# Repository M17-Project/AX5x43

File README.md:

# AX5x43
Test boards for the ON Semiconductor AX5043 and AX5243 RF transceiver chips.
#### The main purpose of this board is to test AX5x43's M17 support.

### Main differences between our board and other available out there
There are two major differences:
- the PWRAMP (AX5043) or TCXO_EN (AX5243) pin can be used as a sigma-delta modulator output for analog demodulation
- GPADC1 and GPADC2 pins can be used for analog frequency modulation (a VCO mode, if you will)

Note: There are no additional operational amplifiers nor filters in our design. Both modulator input and output are available at the pin header. ADC inputs can work in both differential and single-ended modes. Refer to the application note [AND9313/D](https://www.onsemi.com/pub/collateral/and9313-d.pdf).

### AX5043 PCB

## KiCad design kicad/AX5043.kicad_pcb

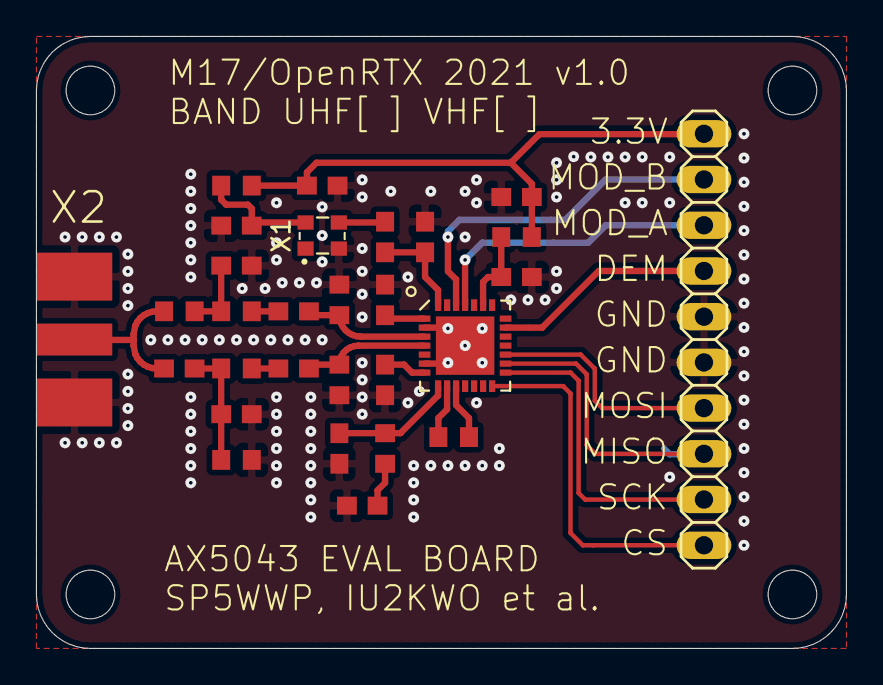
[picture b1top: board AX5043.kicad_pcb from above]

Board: 2 copper layers, 45.0 x 34.0 mm, 29 parts (0 on the bottom side), 26 nets.

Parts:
C1: 10p; C0603
C2: 6.8p; C0603
C3, C4: 100p; C0603
C5, C6: 4.3p; C0603
C7: 11p; C0603
C8: 5.6p; C0603
C9: 5.1p; C0603
C10, C12, C15: 10n; C0603
C11, C13: 100n; C0603
C14: 39p; C0603
JP1: PINHD-1X10; 1X10
R1, R2: 100nH; R0603
R3, R4: 43nH; R0603
R5, R6: 27nH; R0603
R7, R8: BEAD; R0603
R9: 10nH; R0603
R10: 12k; R0603
U1: AX5043; QFN28-5X5-WITH-CENTER-PAD
X1: 12.000MHz; ECS-TXO-2520
X2: SMA; J502-ND-142-0711-821_826

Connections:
+3V3: C11.1, C13.1, JP1.1, R7.2, R8.2
/CLK_REF: C1.2, C2.1, U1.28
/CS: JP1.10, U1.14
/DEMOD_OUT: JP1.4, U1.20
/MISO: JP1.8, U1.16
/MOD_IN_A: JP1.3, U1.25
/MOD_IN_B: JP1.2, U1.26
/MOSI: JP1.7, U1.17
/SCLK: JP1.9, U1.15
GND: C2.2, C3.2, C4.2, C7.1, C8.2, C10.1, C11.2, C12.1, C13.2, C14.2, C15.2, JP1.5, JP1.6, R1.1, R2.2, R6.2, U1.2, U1.6, U1.PAD, X1.2, X2.G@1, X2.G@2, X2.G@3, X2.G@4
unnamed: C1.1, X1.3
unnamed: C3.1, U1.1
unnamed: C4.1, U1.7
unnamed: C5.1, R2.1, U1.3
unnamed: C5.2, R3.1
unnamed: C6.1, R1.2, U1.4
unnamed: C6.2, R4.1
unnamed: C7.2, R3.2, R5.1
unnamed: C8.1, C9.2, R4.2, R6.1
unnamed: C9.1, R5.2, X2.1
unnamed: C10.2, R7.1, X1.4
unnamed: C12.2, R8.1, U1.23
unnamed: C14.1, R10.1, U1.8
unnamed: C15.1, R10.2
unnamed: R9.1, U1.9
unnamed: R9.2, U1.10

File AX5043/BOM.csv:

References,Qty,Description,Manufacturer,MPN
C1,1,10pF 0603,Yageo,CC0603JRNPO9BN100
C2,1,6.8pF 0603,Yageo,CC0603DRNPO9BN6R8
C3 C4,2,100pF 0603,Yageo,CC0603JRNPO9BN101
C5 C6,2,4.3pF 0603,Yageo,CC0603CRNPO9BN4R3
C7,1,11pF 0603,Yageo,CC0603JPNPO9BN110
C8,1,5.6pF 0603,Yageo,CC0603DRNPO9BN5R6
C9,1,5.1pF 0603,Yageo,CC0603CRNPO9BN5R1
C10 C12 C15,3,10nF 0603,Yageo,CC0603KRX7R9BB103
C11 C13,2,100nF 0603,Yageo,CC0603KRX7R9BB104
C14,1,39pF 0603,Yageo,CC0603JRNPO9BN390
JP1,1,CPL-CON-HEADER-THT-MALE,,
R1 R2,2,100nH 0603,Murata,LQW18ASR10G00D
R3 R4,2,43nH 0603,Murata,LQW18AN43NG00D
R5 R6,2,27nH 0603,Murata,LQW18AN27NG00D
R9,1,6.8nH 0603,Murata,LQW18AN6N8C00D
R10,1,12k 0603,Yageo,RC0603FR-0712KL
U1,1,AX5043,onsemi,AX5043-1-TW30
X1,1,12MHz TCXO 2520,ECS,ECS-TXO-2520MV-120-AY-TR
X2,1,SMA female connector PCB edge mount,RF Solutions,CON-SMA-EDGE-S

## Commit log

2021-08-16 Eagle and KiCad project files
2021-08-24 Rescued some missing symbols/footprint in KiCad project
2021-08-24 Add rounded corners
2021-09-09 Reorganised KiCad libraries
2021-09-09 New footprint for TCXO, model is ECS-TXO-2520
2021-09-13 Gerber files for PCB manufacturing
2021-09-13 Fixed some unconnected ground vias, re-generated gerber files
2021-09-13 Removed dangling trace, re-generated gerber files
2021-10-31 Added folder for AX5243 board, moved AX5043 files to a dedicated folder
2022-01-15 Changed value of VCO coil inductor from 10nH to 6.8nH. Added BOM.
